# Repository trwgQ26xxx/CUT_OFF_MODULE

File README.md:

# Information about OE Fiat 126p Modules

## CUT-OFF Module

Schematic of a fuel cut-off module for carburetor engines equipped with a catalytic converter.

Originally drawn in 2018 using Eagle 7.6.0. The project has now been made public and imported into KiCad 9.0.8.

## ESD-48 Module

Schematic of an acoustic choke warning signalizer.

## RNc-12 Module

Recreation of the alternator voltage regulator. The new PCB fits into the original housing and was used to fix the faulty regulator in the car.

Originally designed on June 4, 2018, using KiCad 5.0.0-rc2. The project has now been made public and imported into KiCad 9.0.8.

# Disclaimer

I do not consent to the use of all or part of the project for commercial purposes!

Nie wyrażam zgody na wykorzystanie całości bądź części projektu w celach zarobkowych!

# License

Shield: [![CC BY-NC-SA 4.0][cc-by-nc-sa-shield]][cc-by-nc-sa]

This work is licensed under a
[Creative Commons Attribution-NonCommercial-ShareAlike 4.0 International License][cc-by-nc-sa].

[![CC BY-NC-SA 4.0][cc-by-nc-sa-image]][cc-by-nc-sa]

[cc-by-nc-sa]: http://creativecommons.org/licenses/by-nc-sa/4.0/
[cc-by-nc-sa-image]: https://licensebuttons.net/l/by-nc-sa/4.0/88x31.png
[cc-by-nc-sa-shield]: https://img.shields.io/badge/License-CC%20BY--NC--SA%204.0-lightgrey.svg

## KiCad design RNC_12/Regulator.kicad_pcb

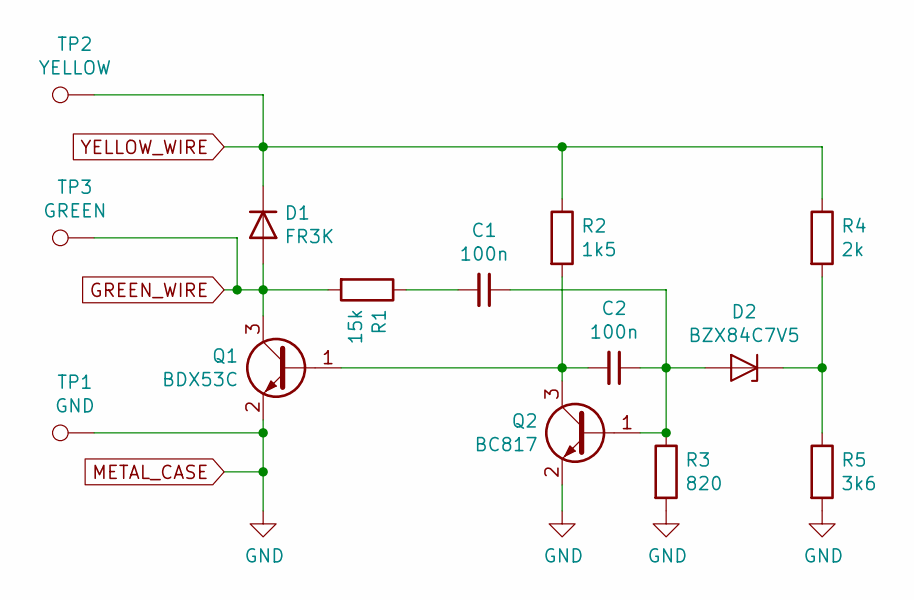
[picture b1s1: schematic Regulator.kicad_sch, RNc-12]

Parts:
C1, C2: 100n; C_1206
D1: FR3K; D_SMC_Handsoldering
D2: BZX84C7V5; D_SOT-23_ANK
Q1: BDX53C; MOJA_TO220_SMD
Q2: BC817; SOT-23
R1: 15k; R_1206
R2: 1k5; R_1206
R3: 820; R_1206
R4: 2k; R_1206
R5: 3k6; R_1206
TP1: GND; ZOLTY_PAD
TP2: YELLOW; ZOLTY_PAD
TP3: GREEN; ZOLTY_PAD

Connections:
GREEN_WIRE: D1.2 (A), Q1.3 (C), R1.2, TP3.1
METAL_CASE: Q1.2 (E), Q2.2 (E), R3.2, R5.2, TP1.1
unnamed: C1.2, R1.1
unnamed: C1.1, C2.1, D2.2 (A), Q2.1 (B), R3.1
unnamed: D2.1 (K), R4.2, R5.1
unnamed: C2.2, Q1.1 (B), Q2.3 (C), R2.2
YELLOW_WIRE: D1.1 (K), R2.1, R4.1, TP2.1

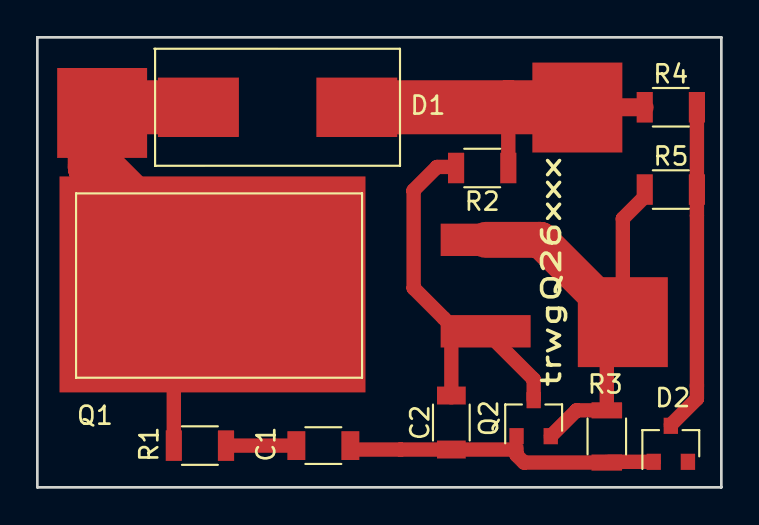
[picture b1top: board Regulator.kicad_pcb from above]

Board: 2 copper layers, 38.0 x 25.0 mm, 14 parts (0 on the bottom side), 7 nets.

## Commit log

2024-04-21 Imported schematic from Eagle added to repository
2024-08-24 License information added
2026-03-26 Added schematid of an acoustic choke warning signalizer
2026-04-11 Added project of RNc-12 alternator voltage regulator
2026-04-11 Added photos of an acoustic choke warning signalizer
2026-04-11 KiCad project of cut-off module updated
2026-04-11 README.md updated
2026-06-07 Piezo wiring connections updated based on tests
